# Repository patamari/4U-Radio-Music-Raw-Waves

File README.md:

4U port of Radio Music / Raw Waves for LW format.
Raw Waves Teensy 4.0 adaptation by Jim Mulvey.
Original module design by Tom Whitwell. cc-by-sa.

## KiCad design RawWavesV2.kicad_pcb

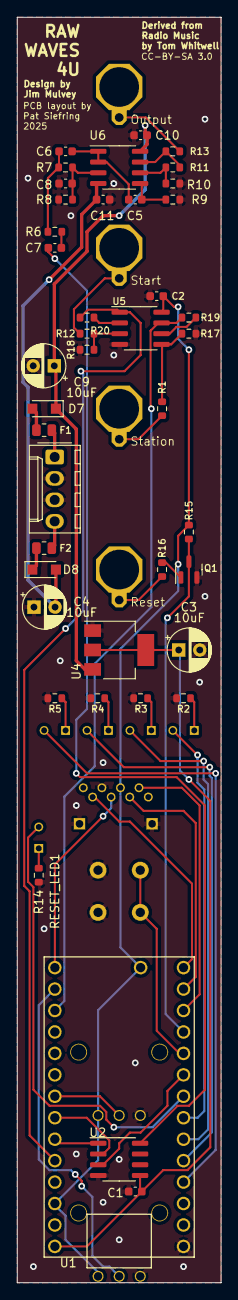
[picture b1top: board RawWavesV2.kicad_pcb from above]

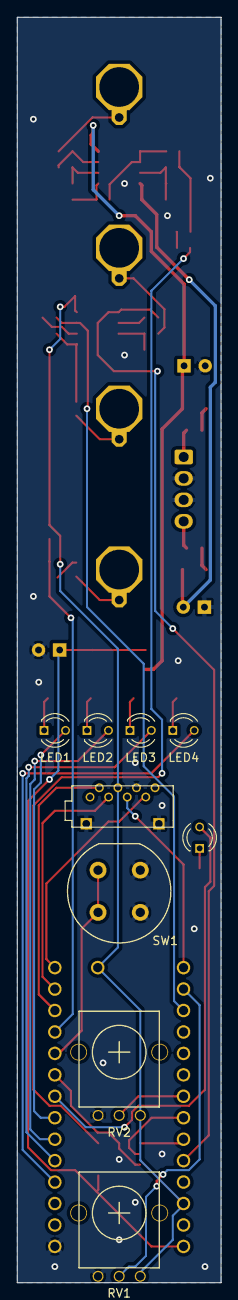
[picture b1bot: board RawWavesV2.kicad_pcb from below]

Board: 2 copper layers, 24.1 x 149.9 mm, 50 parts (9 on the bottom side), 43 nets.

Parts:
C1: 100nf; C_0603_1608Metric
C2, C5, C7, C10, C11: 100nF; C_0603_1608Metric
C3, C4, C9: 10uF; CP_Radial_D5.0mm_P2.50mm
C6, C8: 1nF; C_0603_1608Metric
D7, D8: 1N5819; Nexperia_CFP3_SOD-123W
F1, F2: Polyfuse_Small; R_0805_2012Metric
J3: Micro_SD_Card; YAMAICHI_MICROSD_VERTICAL
LED1: LED1; LED_D3.0mm
LED2: LED2; LED_D3.0mm
LED3: LED3; LED_D3.0mm
LED4: LED4; LED_D3.0mm
Q1: MMBT3904; SOT-23
R1, R8, R12, R16, R19, R20: 100k; R_0603_1608Metric
R2, R3, R4, R5, R10, R14, R15: 10k; R_0603_1608Metric
R6, R7: 5.6k; R_0603_1608Metric
R9: 330k; R_0603_1608Metric
R11: 120k; R_0603_1608Metric
R13: 1k; R_0603_1608Metric
R17, R18: 200k; R_0603_1608Metric
RESET_LED1: RESET_LED; LED_D3.0mm
RV1: R_STATION; Alpha9mmPot
RV2: R_START; Alpha9mmPot
SW1: SW_DIP_x01; Push_E-Switch_KS01Q01
U1: Teensy4.0; Teensy4.0-RawWavesV2
U2: PT8211; SOIC-8_3.9x4.9mm_P1.27mm
U4: LM1117MP-5.0; SOT-223-3_TabPin2
U5: MCP6002-xSN; SOIC-8_3.9x4.9mm_P1.27mm
U6: TL072; SOIC-8_3.9x4.9mm_P1.27mm

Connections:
3.3V: C2.2, J3.4 (VDD), R15.1, RV1.3, RV2.3, U1.16 (3V3), U1.31 (3V3), U5.8 (V+)
5.0V: C1.1, C3.1, U1.33 (VIN), U2.5 (VDD), U4.2 (VO)
+12V: C9.1, C10.2, D7.1 (K), U4.3 (VI), U6.8 (V+)
-12V: C4.2, C11.1, D8.2 (A), U6.4 (V-)
DAC_BIT_CLOCK: U1.28 (21_A7_RX5_BCLK1), U2.1 (BCK)
DAC_DATA_IN: U1.9 (7_RX2_OUT1A), U2.3 (DIN)
DAC_RIGHT_OUT: C7.1, U2.8 (RCH)
DAC_WORD_SELECT: U1.27 (20_A6_TX5_LRCLK1), U2.2 (WS)
GND: C1.2, C2.1, C3.2, C4.1, C8.1, C9.2, C10.1, C11.2, J3.6 (VSS), J3.9 (SHIELD), Q1.2 (E), R2.2, R3.2, R4.2, R5.2, R8.1, R9.2, R10.2, R14.2, R17.2, R18.2, RV1.1, RV2.1, SW1.1, U1.1 (GND), U2.4 (GND), U4.1 (GND), U5.4 (V-)
LED1: LED1.2 (A), U1.7 (5_IN2)
LED2: LED2.2 (A), U1.6 (4_BCLK2)
LED3: LED3.2 (A), U1.5 (3_LRCLK2)
LED4: LED4.2 (A), U1.4 (2_OUT2)
LED_RESET: RESET_LED1.2 (A), U1.8 (6_OUT1D)
unnamed: C6.1, R6.2, R7.1
unnamed: C7.2, R6.1
unnamed: D7.2 (A), F1.1
unnamed: D8.1 (K), F2.1
unnamed: J3.5 (CLK), U1.20 (13_SCK_CRX1_LED)
unnamed: J3.3 (CMD), U1.13 (11_MOSI_CTX1)
unnamed: J3.7 (DAT0), U1.14 (12_MISO_MQSL)
unnamed: J3.2 (DAT3/CD), U1.12 (10_CS_MQSR)
unnamed: LED1.1 (K), R2.1
unnamed: LED2.1 (K), R3.1
unnamed: LED3.1 (K), R4.1
unnamed: LED4.1 (K), R5.1
unnamed: Q1.1 (B), R16.1
unnamed: R11.1, R13.2, U6.7
unnamed: R14.1, RESET_LED1.1 (K)
unnamed: RV1.2, U1.21 (14_A0_TX3_SPDIF_OUT)
unnamed: RV2.2, U1.26 (19_A5_SCL0)
unnamed: R12.2, R18.1, U5.3 (+)
unnamed: R20.1, U5.2 (-)
unnamed: R1.2, R17.1, U5.5 (+)
unnamed: R19.1, U5.6 (-)
unnamed: C8.2, R7.2, R8.2, U6.3 (+)
unnamed: C5.1, C6.2, U6.1, U6.2 (-)
unnamed: C5.2, R9.1, U6.5 (+)
unnamed: R10.1, R11.2, U6.6 (-)
RESET_BUTTON: SW1.2, U1.10 (8_TX2_IN1)
RESET_CV_PROTECTED: Q1.3 (C), R15.2, U1.11 (9_OUT1C)
START_CV_PROTECTED: R20.2, U1.29 (22_A8_CTX1), U5.1
STATION_CV_PROTECTED: R19.2, U1.22 (15_A1_RX3_SPDIF_IN), U5.7

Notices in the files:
RawWavesV2.kicad_pcb:
CC-BY-SA 3.0
